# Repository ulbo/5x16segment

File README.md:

Linkable 5x16-Segment LED Display Module
========================================

Single display board

Two boards connected to form a 10 character display

Hardware
--------

The module uses an Atmel ATmega32 MCU to control all LED segments. Input is done via RS232 interface with a voltage level of 5V.

Supply voltage: 5VDC, max. 200mA per module

Board layout is designed using KiCAD. It is tested for LDS8103-AX 16-segment displays (see /board/lds-8103.jpg), but should work with any common-cathode 16-segment display with same mechanical dimensions and pinout, e.g. Kingbright PSC08-11GWA. Because all pins, except the cathode at pin 11, are directly controlled by the MCU, LEDs with other pinouts can be used with adapted firmware.

Please note: The LED displays are soldered on the opposite board site than the ATmega.

Firmware
--------

Communication to modules is unidirectional with _9600 bps, 8N1_. Modules are daisy-chained, the RS232 output of the leftmost module is connected to the input of its right neighbour. Every module displays all incoming ASCII characters. If its 5-character memory is full, it passes all further incoming chars to its output, where it is received by the next display.

There are a few control characters, which are always passed immediately:

 * 0x01..0x06 : set display brightness, 1 is lowest
 * 0x10, 0x13 : <CR> or <LF> character reset the "cursor" to leftmost position

Compilation under Windows by Atmel Studio 7, Project file: /firmware/16segment.atsln
For Linux, /firmware/makefile is provided, see instructions there.

Firmware is flashed using the standard 6-pin ISP connector. File is /firmware/Release/16segment.hex

Fuse settings:

 * BODLEVEL = 2.7 V,
 * CLKSEL = Ext. Crystal, 8.0-16.0 MHz, 16K CK, 65ms start up time
 * BOOTSZ = 256 words
 * SPIEN enabled
 * TAGEN disabled
 * others: disabled

Character Set
-------------

 * 0x20 .. 0x7F : normal ASCII characters, small caps are currently rendered uppercase (may be changed in future release)
 * 0x80 .. 0x9F : a few "graphic" characters, arrows, etc.
 * 0xA0 .. 0xff : same as 0x20..0x7f, but with decimal point on

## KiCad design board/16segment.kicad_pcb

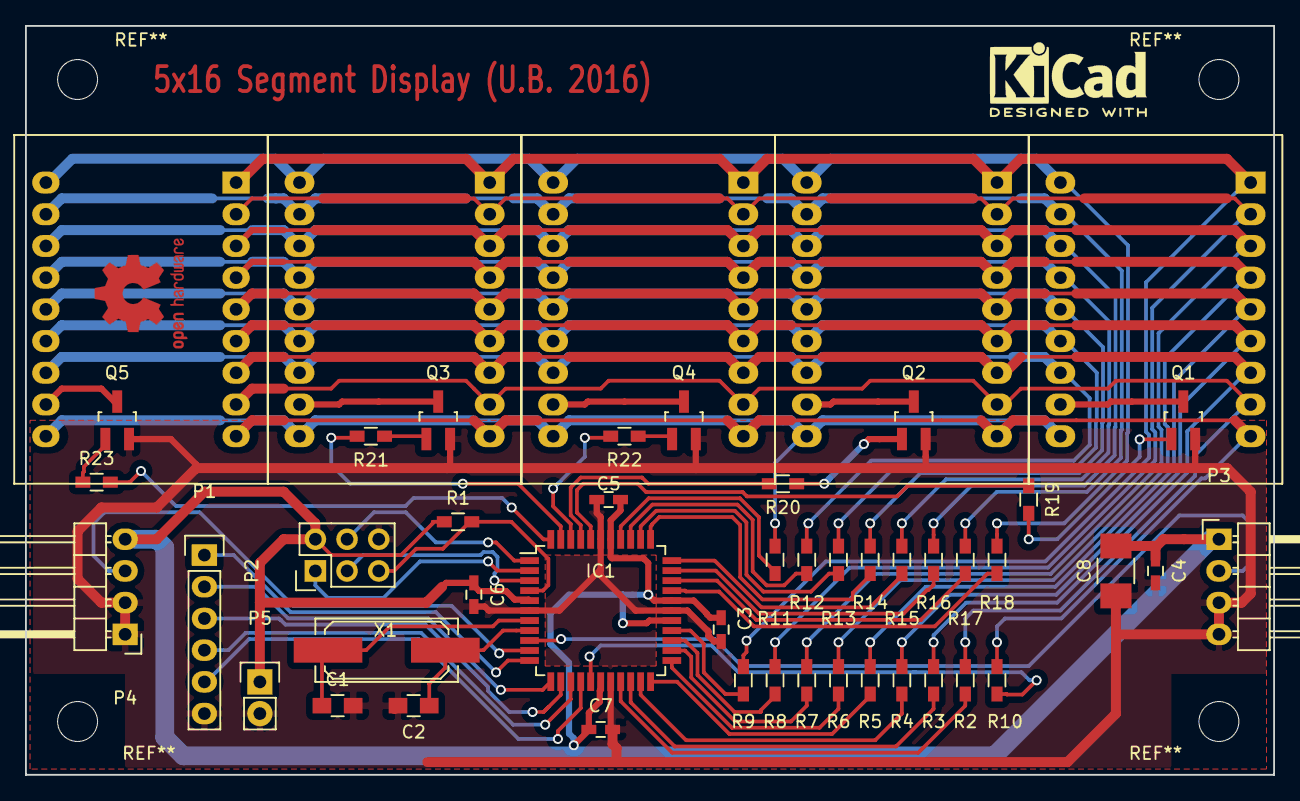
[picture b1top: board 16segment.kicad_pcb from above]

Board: 2 copper layers, 100.0 x 60.0 mm, 48 parts (0 on the bottom side), 64 nets.

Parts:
C1, C2: 15pF; C_0805_HandSoldering
C3, C4, C5, C6, C7: 100nF; C_0603_HandSoldering
C8: 10uF; C_1210_HandSoldering
IC1: ATMEGA16-A; TQFP-44_10x10mm_Pitch0.8mm
LED1, LED2, LED3, LED4, LED5: LDS-8103AX; LDS8103-AX_rev
P1: CONN_01X06; Pin_Header_Straight_1x06
P2: AVR ISP; Pin_Header_Straight_2x03
P3: DATA_IN; Pin_Header_Angled_1x04
P4: DATA_OUT; Pin_Header_Angled_1x04
P5: CONN_01X02; Pin_Header_Straight_1x02
Q1, Q2, Q3, Q4, Q5: BC817-40; SOT-23_Handsoldering
R1: 10k; R_0603_HandSoldering
R2, R3, R4, R5, R6, R7, R8, R9, R10, R11, R12, R13, R14, R15, R16, R17, R18: 180; R_0603_HandSoldering
R19, R20, R21, R22, R23: 470; R_0603_HandSoldering
X1: 16 MHz; Q_49U3HMS

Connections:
/LED_1: IC1.40, R19.2
/LED_2: IC1.41, R20.2
/LED_3: IC1.42, R22.2
/LED_4: IC1.43, R21.2
/LED_5: IC1.44, R23.2
/LED_A1: LED1.1, LED2.1, LED3.1, LED4.1, LED5.1, R9.1
/LED_A2: LED1.18, LED2.18, LED3.18, LED4.18, LED5.18, R18.1
/LED_B: LED1.16, LED2.16, LED3.16, LED4.16, LED5.16, R16.1
/LED_C: LED1.13, LED2.13, LED3.13, LED4.13, LED5.13, R13.1
/LED_D1: LED1.9, LED2.9, LED3.9, LED4.9, LED5.9, R10.1
/LED_D2: LED1.10, LED2.10, LED3.10, LED4.10, LED5.10, R11.1
/LED_DP: LED1.12, LED2.12, LED3.12, LED4.12, LED5.12, R12.1
/LED_E: LED1.8, LED2.8, LED3.8, LED4.8, LED5.8, R2.1
/LED_F: LED1.4, LED2.4, LED3.4, LED4.4, LED5.4, R6.1
/LED_G1: LED1.5, LED2.5, LED3.5, LED4.5, LED5.5, R5.1
/LED_G2: LED1.15, LED2.15, LED3.15, LED4.15, LED5.15, R15.1
/LED_H: LED1.3, LED2.3, LED3.3, LED4.3, LED5.3, R7.1
/LED_J: LED1.2, LED2.2, LED3.2, LED4.2, LED5.2, R8.1
/LED_K: LED1.17, LED2.17, LED3.17, LED4.17, LED5.17, R17.1
/LED_L: LED1.14, LED2.14, LED3.14, LED4.14, LED5.14, R14.1
/LED_M: LED1.6, LED2.6, LED3.6, LED4.6, LED5.6, R4.1
/LED_N: LED1.7, LED2.7, LED3.7, LED4.7, LED5.7, R3.1
/MISO: IC1.2, P2.1
/MOSI: IC1.1, P2.4
/RESET: IC1.4, P2.5, R1.2
/RxD: IC1.9, P3.2
/SCK: IC1.3, P2.3
/TxD: IC1.10, P4.3
GND: C1.2, C2.2, C3.2, C4.2, C5.2, C6.2, C7.2, C8.2, IC1.6, IC1.18, IC1.28, IC1.39, P1.6, P2.6, P3.3, P3.4, P4.1, P4.2, P5.2, Q1.2, Q2.2, Q3.2, Q4.2, Q5.2
unnamed: C1.1, IC1.7, X1.1
unnamed: C2.1, IC1.8, X1.2
unnamed: IC1.11, P1.1
unnamed: IC1.12, P1.2
unnamed: IC1.13, P1.3
unnamed: IC1.14, P1.4
unnamed: IC1.15, P1.5
unnamed: IC1.16, R10.2
unnamed: IC1.19, R2.2
unnamed: IC1.20, R3.2
unnamed: IC1.21, R4.2
unnamed: IC1.22, R5.2
unnamed: IC1.23, R6.2
unnamed: IC1.24, R7.2
unnamed: IC1.25, R8.2
unnamed: IC1.26, R9.2
unnamed: IC1.30, R18.2
unnamed: IC1.31, R17.2
unnamed: IC1.32, R16.2
unnamed: IC1.33, R15.2
unnamed: IC1.34, R14.2
unnamed: IC1.35, R13.2
unnamed: IC1.36, R12.2
unnamed: IC1.37, R11.2
unnamed: LED1.11, Q1.3
unnamed: LED2.11, Q2.3
unnamed: LED3.11, Q3.3
unnamed: LED4.11, Q4.3
unnamed: LED5.11, Q5.3
unnamed: Q1.1, R19.1
unnamed: Q2.1, R20.1
unnamed: Q3.1, R21.1
unnamed: Q4.1, R22.1
unnamed: Q5.1, R23.1
VCC: C3.1, C4.1, C5.1, C6.1, C7.1, C8.1, IC1.5, IC1.17, IC1.27, IC1.29, IC1.38, P2.2, P3.1, P4.4, P5.1, R1.1

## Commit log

2017-01-23 Initial release.
2017-01-23 Added pictures
2017-01-24 Set theme jekyll-theme-midnight
